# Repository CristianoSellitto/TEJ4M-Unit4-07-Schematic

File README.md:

# TEJ4M-Unit4-07-Schematic

Electronic schematic & PCB for Unit4-07

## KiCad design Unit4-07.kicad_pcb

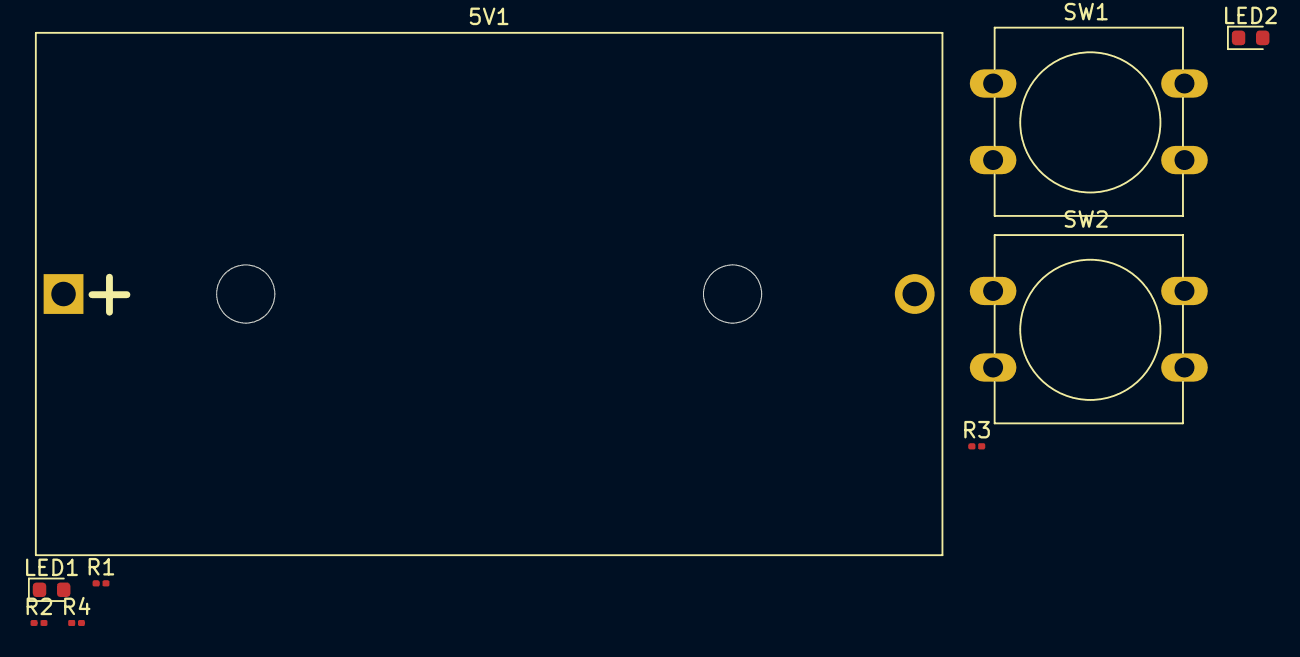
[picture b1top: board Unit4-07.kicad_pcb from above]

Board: 2 copper layers, 9 parts (0 on the bottom side), 6 nets, no tracks yet.

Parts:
5V1: Battery; BatteryHolder_Bulgin_BX0036_1xC
LED1: RED; LED_0603_1608Metric
LED2: BLUE; LED_0603_1608Metric
R1, R2, R3, R4: 220Ω; R_0201_0603Metric
SW1, SW2: SW_Push; SW_PUSH-12mm

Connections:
unnamed: 5V1.1, SW1.2, SW2.2
unnamed: 5V1.2, R1.1, R3.2
unnamed: LED1.1, R4.1
unnamed: LED2.1, R3.1
unnamed: R1.2, SW1.1
unnamed: R2.2, SW2.1

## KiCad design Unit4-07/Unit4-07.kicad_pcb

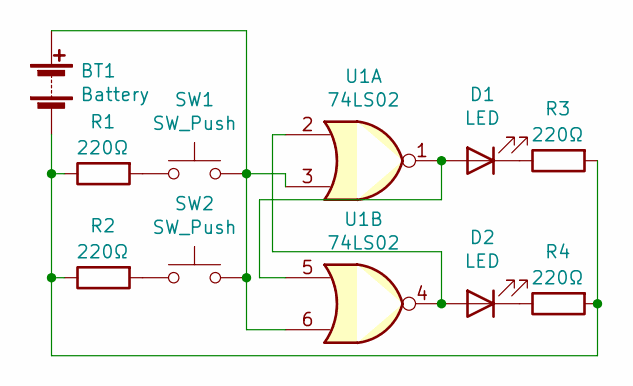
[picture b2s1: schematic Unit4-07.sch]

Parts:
BT1: Battery; BatteryHolder_Bulgin_BX0036_1xC
D1, D2: LED; LED_0201_0603Metric
R1, R2, R3, R4: 220Ω; R_0201_0603Metric
SW1, SW2: SW_Push; SW_PUSH-12mm
U1: 74LS02; SOIC-14_3.9x8.7mm_P1.27mm

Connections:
unnamed: BT1.1 (+), SW1.2, SW2.2, U1.3, U1.6
unnamed: BT1.2 (-), R1.1, R2.1, R3.2, R4.2
unnamed: D1.1 (K), R3.1
unnamed: D1.2 (A), U1.1, U1.5
unnamed: D2.1 (K), R4.1
unnamed: D2.2 (A), U1.2, U1.4
unnamed: R1.2, SW1.1
unnamed: R2.2, SW2.1

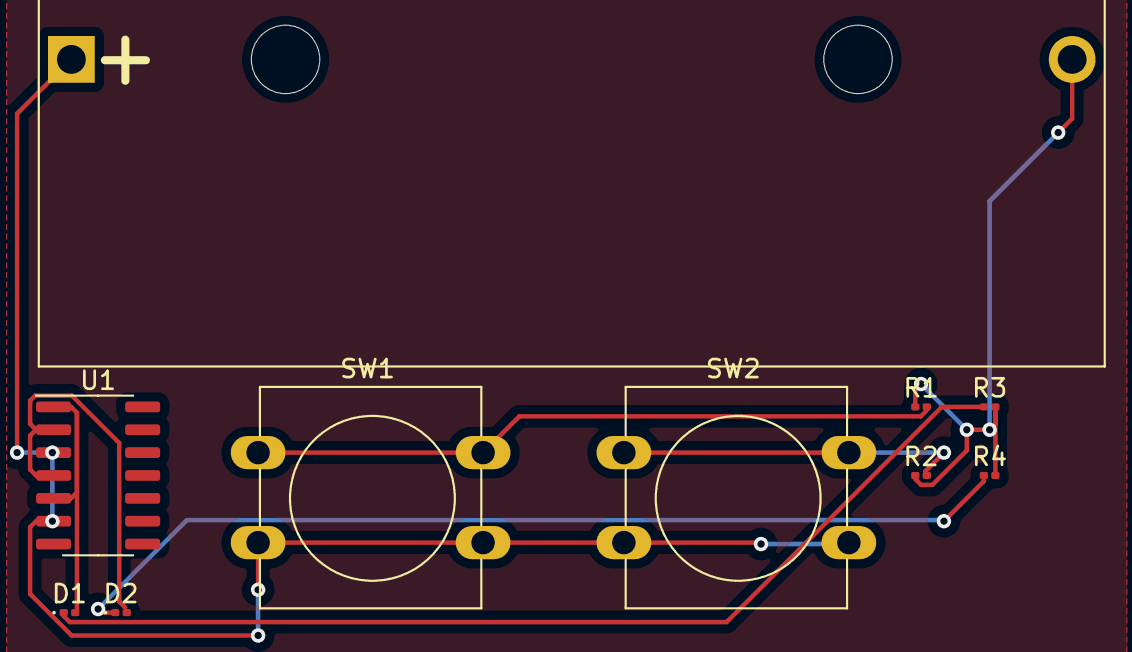
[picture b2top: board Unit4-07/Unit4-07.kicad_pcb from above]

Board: 2 copper layers, 10 parts (0 on the bottom side), 8 nets.

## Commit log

2023-10-26 SSH Import
2023-11-02 Removed dupe project
